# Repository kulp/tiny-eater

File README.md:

# tiny-eater

This is a hobby electronics project to reduce the power of a composite video
signal by 1dB-10dB, to compensate for equipment that is overdriving the signal.
It is an attenuator, a "tiny eater" of signal power.

## What it does

A [composite video signal](https://en.wikipedia.org/wiki/Composite_video) entering
one RCA jack passes through a [T-pad](https://en.wikipedia.org/wiki/T_pad)
and leaves through the other RCA jack. Three trimmer potentiometers set the
attenuation level; with 50 Ohm series trimmers and a 1000 Ohm shunt trimmer, the
range covers 1dB to 10dB, plus a bit extra.

`sim/resistor_table.csv` lists the trimmer settings for each dB. Four test
points (IN, MID, OUT, GND) let the settings be checked with a multimeter.

## The repository

- `attenuator.kicad_sch`, `attenuator.kicad_pcb`: the [KiCad](https://www.kicad.org) schematic and board.
- `sim/`: `resistor_table.csv` plus the [ngspice](https://ngspice.sourceforge.io) netlists generated from it for each 1dB step.
- `enclosure/`: a 3D-printed case in [OpenSCAD](https://openscad.org) format.
- `models/`: datasheets and 3D models for the parts (or links to them).
- `test/`: design checks.

Run `make` to build production files and renders; run `make test` for
engineering and design checks.

## LLM usage

The PCB design itself was modified heavily in KiCad 10 by a human, but an
original version was drafted by Qwen3.8-27B. Test and build support was drafted
by several Qwen3.8 models.

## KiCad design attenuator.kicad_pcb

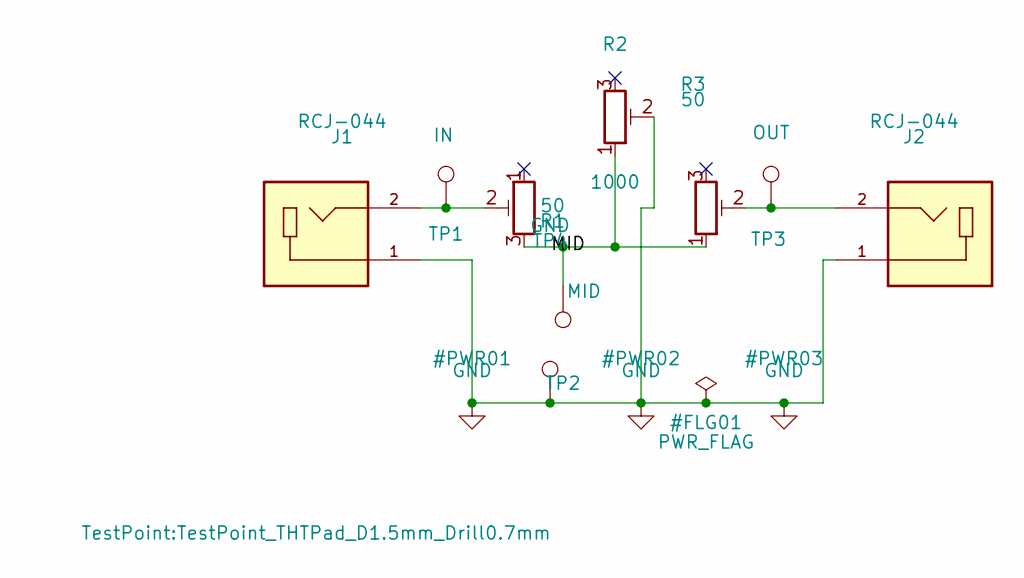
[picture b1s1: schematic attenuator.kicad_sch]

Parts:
J1, J2: RCJ-044; SAMESKY_RCJ-044
R1, R3: 50; Potentiometer_Bourns_3296W_Vertical
R2: 1000; Potentiometer_Bourns_3296W_Vertical
TP1: IN; TestPoint_THTPad_D1.5mm_Drill0.7mm
TP2: MID; TestPoint_THTPad_D1.5mm_Drill0.7mm
TP3: OUT; TestPoint_THTPad_D1.5mm_Drill0.7mm
TP4: GND; TestPoint_THTPad_D1.5mm_Drill0.7mm

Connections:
/MID: R1.3, R2.1, R3.1, TP2.1 (1_1)
GND: J1.1, J2.1, R2.2, TP4.1 (1_1)
unnamed: J1.2, R1.2, TP1.1 (1_1)
unnamed: J2.2, R3.2, TP3.1 (1_1)

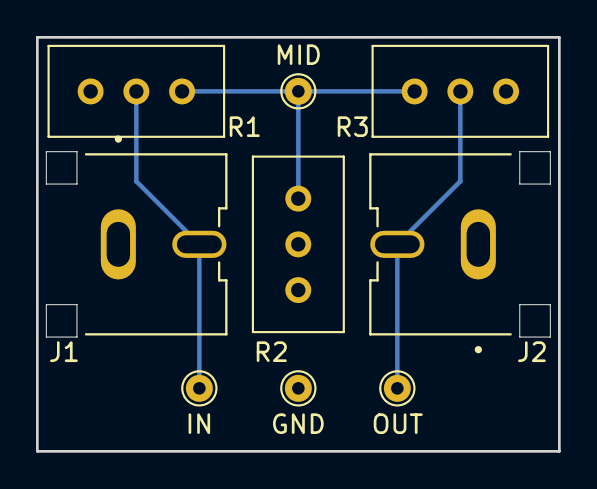
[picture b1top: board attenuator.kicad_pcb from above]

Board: 2 copper layers, 29.0 x 23.0 mm, 9 parts (0 on the bottom side), 4 nets.
